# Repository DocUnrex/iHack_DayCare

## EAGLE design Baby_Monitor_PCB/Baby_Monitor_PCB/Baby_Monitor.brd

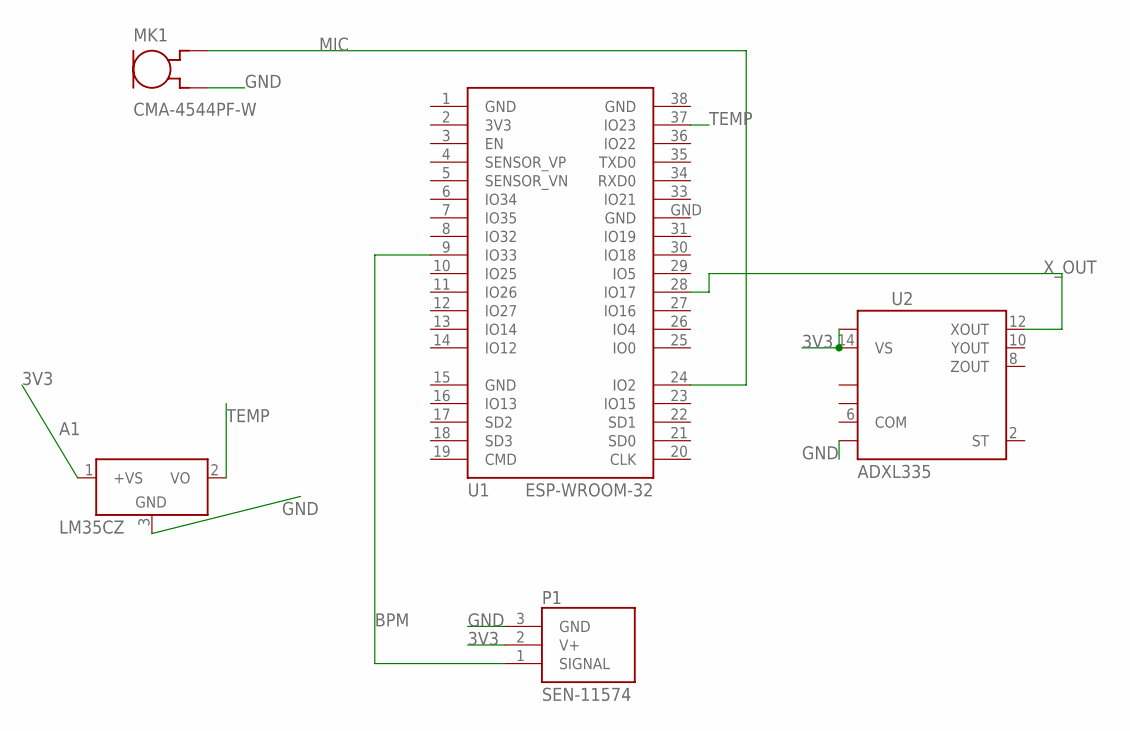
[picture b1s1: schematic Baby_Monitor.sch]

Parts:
A1: LM35CZ; TO92
MK1: CMA-4544PF-W; MIC_CMA-4544PF-W
P1: SEN-11574; XDCR_SEN-11574
U1: ESP-WROOM-32
U2: ADXL335; LFCSP-16

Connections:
3V3: A1.1 (+VS), P1.2 (V+), U1.2 (3V3), U2.14 (VS), U2.15 (VS)
BPM: P1.1 (SIGNAL), U1.9 (IO33)
GND: A1.3 (GND), MK1.2 (GND), P1.3 (GND), U1.1 (GND), U1.15 (GND), U1.38 (GND), U1.GND, U2.7 (COM)
MIC: MK1.1 (OUT), U1.24 (IO2)
TEMP: A1.2 (VO), U1.37 (IO23)
X_OUT: U1.28 (IO17), U2.12 (XOUT)

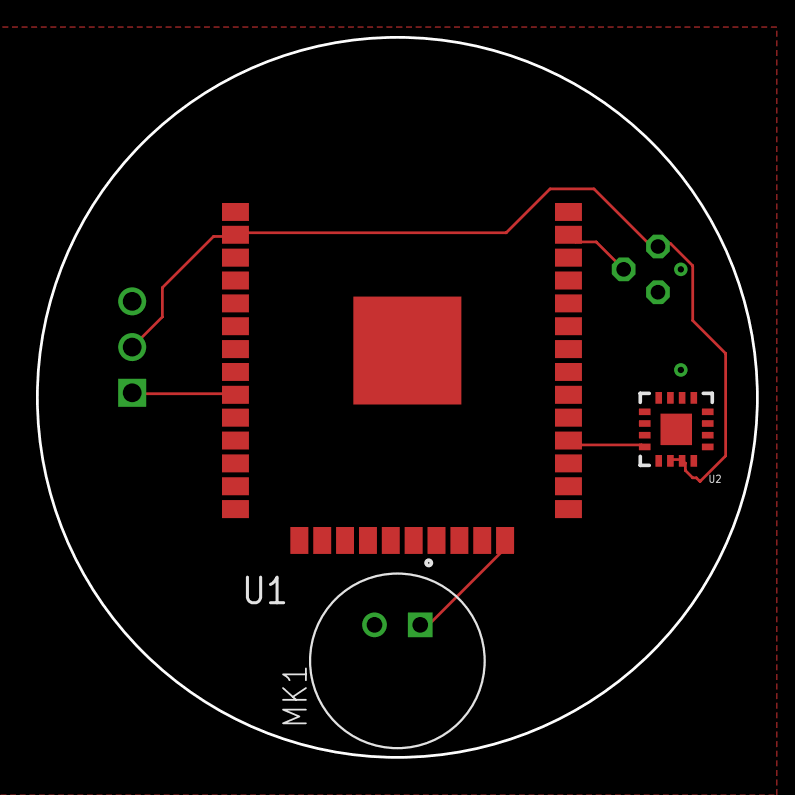
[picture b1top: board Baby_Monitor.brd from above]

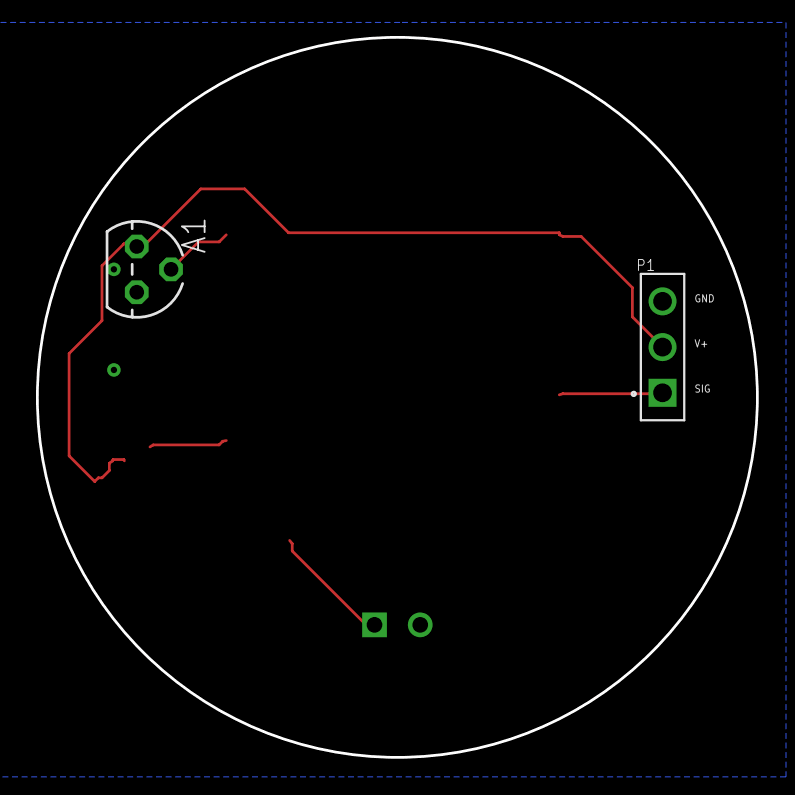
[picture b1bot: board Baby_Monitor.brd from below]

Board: 2 copper layers, 40.0 x 40.0 mm, 5 parts (2 on the bottom side), 6 nets.

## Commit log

2021-05-15 uploaded NodeMCU code
2021-05-15 Uploaded final 3D models of the proposed product
2021-05-15 Uploaded Arduino nano code
2021-05-15 Added UI/UX files

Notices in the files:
parts and their libraries:
esp32: Creative Commons Attribution-ShareAlike 4.0 International
